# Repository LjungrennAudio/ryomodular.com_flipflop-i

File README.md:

# ryomodular.com_flipflop-i
 one of multiplesets of designings for flipflop modules to be consolidated

2408310052

this is just one of multiple flipflop ideas ive seen saved so someehow ive gotta consolidate em all - first thing is to get em all in one place, so why not gihub - is as good as any other /shrug?

i hope this isnt the peak of what i remember of fliplop designs cos i really love flipflops and want to do them justice...

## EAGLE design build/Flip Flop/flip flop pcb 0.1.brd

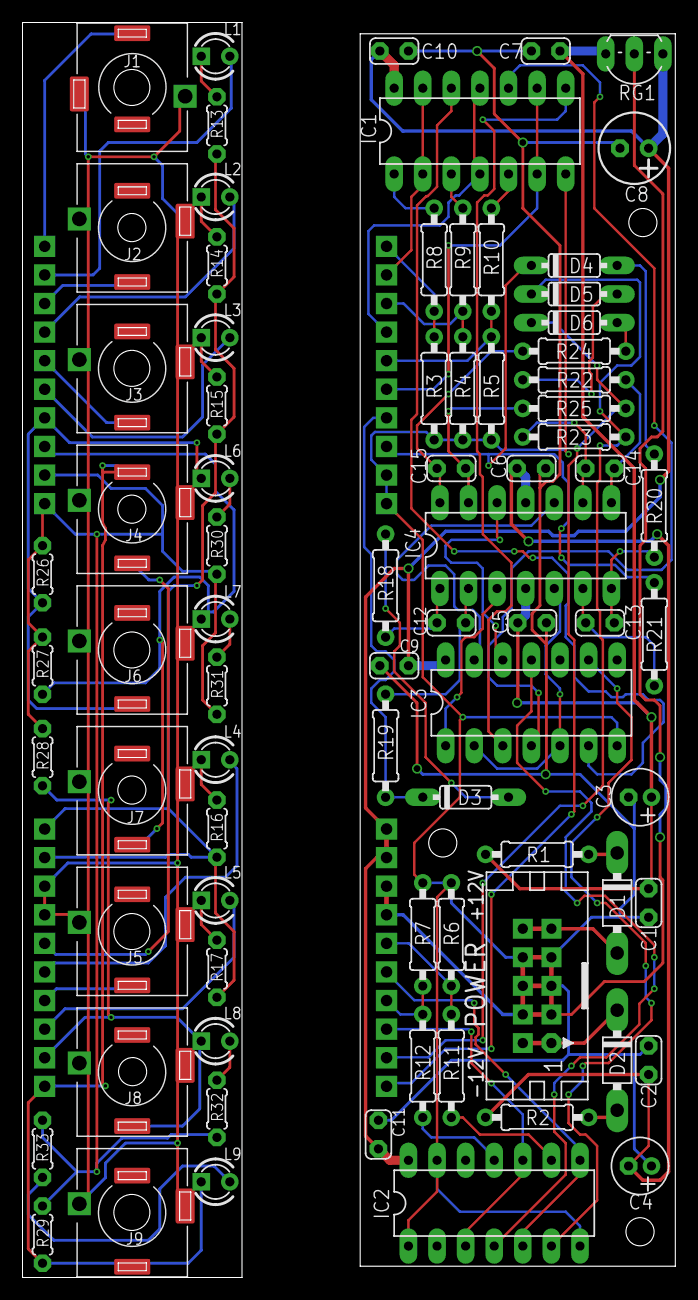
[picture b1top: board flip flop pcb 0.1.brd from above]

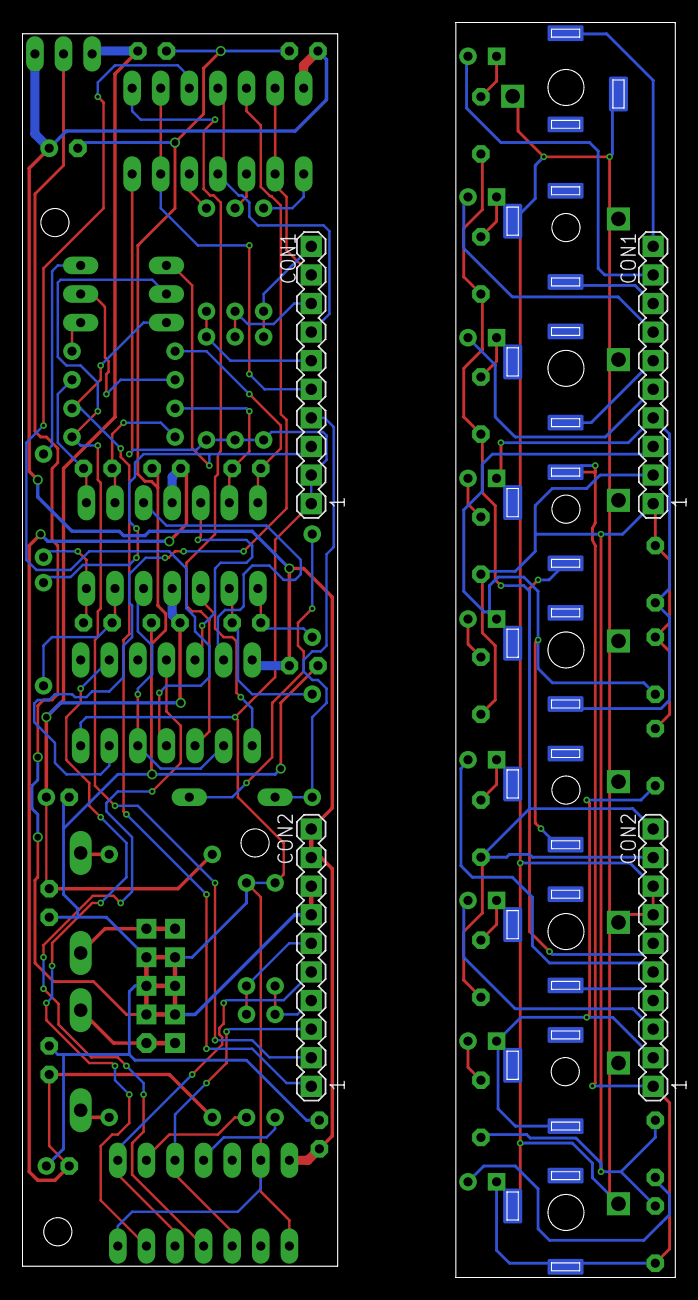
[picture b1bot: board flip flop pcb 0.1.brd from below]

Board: 2 copper layers, 58.0 x 111.5 mm, 82 parts (4 on the bottom side), 71 nets.

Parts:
C1, C2, C5, C6, C7, C9, C10, C11: 100nF; C025-024X044
C3, C4: 10uF; E2-5
C8: 100uF; E2,5-6
C12, C13, C14, C15: 15pF; C025-024X044
CON1-PCB1, CON1-PCB2: CON1; MA10-1
CON2-PCB1, CON2-PCB2: CON2; MA10-1
D1, D2: 1N5818; DO41-7
D3, D4, D5, D6: 1N4148; DO35-7
IC1, IC2: CD40106; DIL14
IC3: CD4013; DIL14
IC4: TL064; DIL14
J1, J2, J3, J4, J5, J6, J7, J8, J9: ERTHENVAR_3.5MM_JACKSLOTS; ERTHENVAR-SLOTS
L1, L2, L3, L4, L5: green; LED3MM
L6, L7, L8, L9: orange; LED3MM
POWER: power; CON10L
R1, R2: 10R; 0207/9
R3, R4, R5, R6, R7, R8, R9, R10, R11, R12, R19, R21, R23, R25: 100k; 0207/9
R13, R14, R15, R16, R17, R30, R31, R32, R33: 1k; 0204/5
R18, R20, R22, R24: 1k; 0207/9
R26, R27, R28, R29: 22k; 0204/5
RG1: LM2931 5V; TO92-LINE

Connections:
0V: C1.2, C2.1, C3.-, C4.+, C5.1, C6.2, C7.1, C8.-, C9.1, C10.1, C11.1, CON1-PCB1.1, CON1-PCB1.2, CON1-PCB2.1, CON1-PCB2.2, CON2-PCB1.7, CON2-PCB1.8, CON2-PCB2.7, CON2-PCB2.8, IC1.7, IC2.1, IC2.7, IC2.13, IC3.7, J1.RING1B, J1.RING1T, J1.RING2H, J2.RING1B, J2.RING1T, J2.RING2H, J3.RING1B, J3.RING1T, J3.RING2H, J4.RING1B, J4.RING1T, J4.RING2H, J5.RING1B, J5.RING1T, J5.RING2H, J6.RING1B, J6.RING1T, J6.RING2H, J7.RING1B, J7.RING1T, J7.RING2H, J8.RING1B, J8.RING1T, J8.RING2H, J9.RING1B, J9.RING1T, J9.RING2H, POWER.3, POWER.4, POWER.5, POWER.6, POWER.7, POWER.8, R3.1, R4.1, R5.1, R6.1, R7.1, R26.1, R27.1, R28.1, R29.1, R30.2, R31.2, R32.2, R33.2, RG1.2
+5V: C8.+, C9.2, C10.2, C11.2, CON2-PCB1.9, CON2-PCB1.10, CON2-PCB2.9, CON2-PCB2.10, IC1.14, IC2.14, IC3.14, R13.1, R14.1, R15.1, R16.1, R17.1, RG1.3
+12V: C1.1, C3.+, C5.2, C7.2, IC4.4, R1.2, RG1.1
-12V: C2.2, C4.-, C6.1, IC4.11, R2.2
C1-1: CON1-PCB1.6, J3.TIPB, J3.TIPT
C1-2: CON1-PCB2.6, R5.2, R10.1
C2-1: CON2-PCB1.4, J5.TIPB, J5.TIPT
C2-2: CON2-PCB2.4, R7.2, R12.1
D2-1: CON2-PCB1.6, J4.TIPB, J4.TIPT
D2-2: CON2-PCB2.6, R6.2, R11.1
L1-1: CON1-PCB1.9, L1.K
L1-2: CON1-PCB2.9, IC1.2, IC1.13
L2-1: CON1-PCB1.7, L2.K
L2-2: CON1-PCB2.7, IC1.4, IC1.11
L3-1: CON1-PCB1.5, L3.K
L3-2: CON1-PCB2.5, IC1.6, IC1.9
L6-1: CON2-PCB1.5, L4.K
L6-2: CON2-PCB2.5, IC2.5, IC2.8
L7-1: CON2-PCB1.3, L5.K
L7-2: CON2-PCB2.3, IC2.3, IC2.10
unnamed: IC1.1, R8.2
unnamed: IC3.2, IC3.5, IC4.5
unnamed: IC1.3, R9.2
unnamed: IC1.5, R10.2
unnamed: IC2.9, R11.2
unnamed: IC2.11, R12.2
unnamed: IC1.12, IC3.6
unnamed: IC1.10, IC3.4
unnamed: IC1.8, IC3.3
unnamed: IC2.4, IC3.11
unnamed: IC2.6, IC3.9
unnamed: IC3.1, IC4.3
unnamed: C12.2, IC4.2, R19.1
unnamed: C12.1, IC4.1, R18.1
unnamed: D3.A, R18.2
unnamed: C13.2, IC4.6, R21.1
unnamed: C13.1, IC4.7, R20.1
unnamed: D4.A, R20.2
unnamed: IC3.13, IC4.10
unnamed: IC3.12, IC4.12
unnamed: C15.2, IC4.13, R25.1
unnamed: C15.1, IC4.14, R24.1
unnamed: D6.A, R24.2
unnamed: D1.C, R1.1
unnamed: C14.2, IC4.9, R23.1
unnamed: C14.1, IC4.8, R22.1
unnamed: D5.A, R22.2
unnamed: D1.A, POWER.9, POWER.10
unnamed: D2.C, POWER.1, POWER.2
unnamed: D2.A, R2.1
unnamed: L1.A, R13.2
unnamed: L2.A, R14.2
unnamed: L3.A, R15.2
unnamed: L6.K, R30.1
unnamed: L7.K, R31.1
unnamed: L4.A, R16.2
unnamed: L5.A, R17.2
unnamed: L8.K, R32.1
unnamed: L9.K, R33.1
Q1-1: CON1-PCB1.4, J6.TIPB, J6.TIPT, L6.A, R26.2
Q1-2: CON1-PCB2.4, D3.C, R19.2
Q2-1: CON2-PCB1.2, J8.TIPB, J8.TIPT, L8.A, R28.2
Q2-2: CON2-PCB2.2, D5.C, R23.2
QB1-1: CON1-PCB1.3, J7.TIPB, J7.TIPT, L7.A, R27.2
QB1-2: CON1-PCB2.3, D4.C, R21.2
QB2-1: CON2-PCB1.1, J4.NORMLB, J4.NORMLT, J9.TIPB, J9.TIPT, L9.A, R29.2
QB2-2: CON2-PCB2.1, D6.C, R25.2
R1-1: CON1-PCB1.8, J2.TIPB, J2.TIPT
R1-2: CON1-PCB2.8, R4.2, R9.1
S1-1: CON1-PCB1.10, J1.TIPB, J1.TIPT
S1-2: CON1-PCB2.10, R3.2, R8.1

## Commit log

2024-08-31 init commit for flippenfloppen
    yup, it grows!
2025-01-13 filing
